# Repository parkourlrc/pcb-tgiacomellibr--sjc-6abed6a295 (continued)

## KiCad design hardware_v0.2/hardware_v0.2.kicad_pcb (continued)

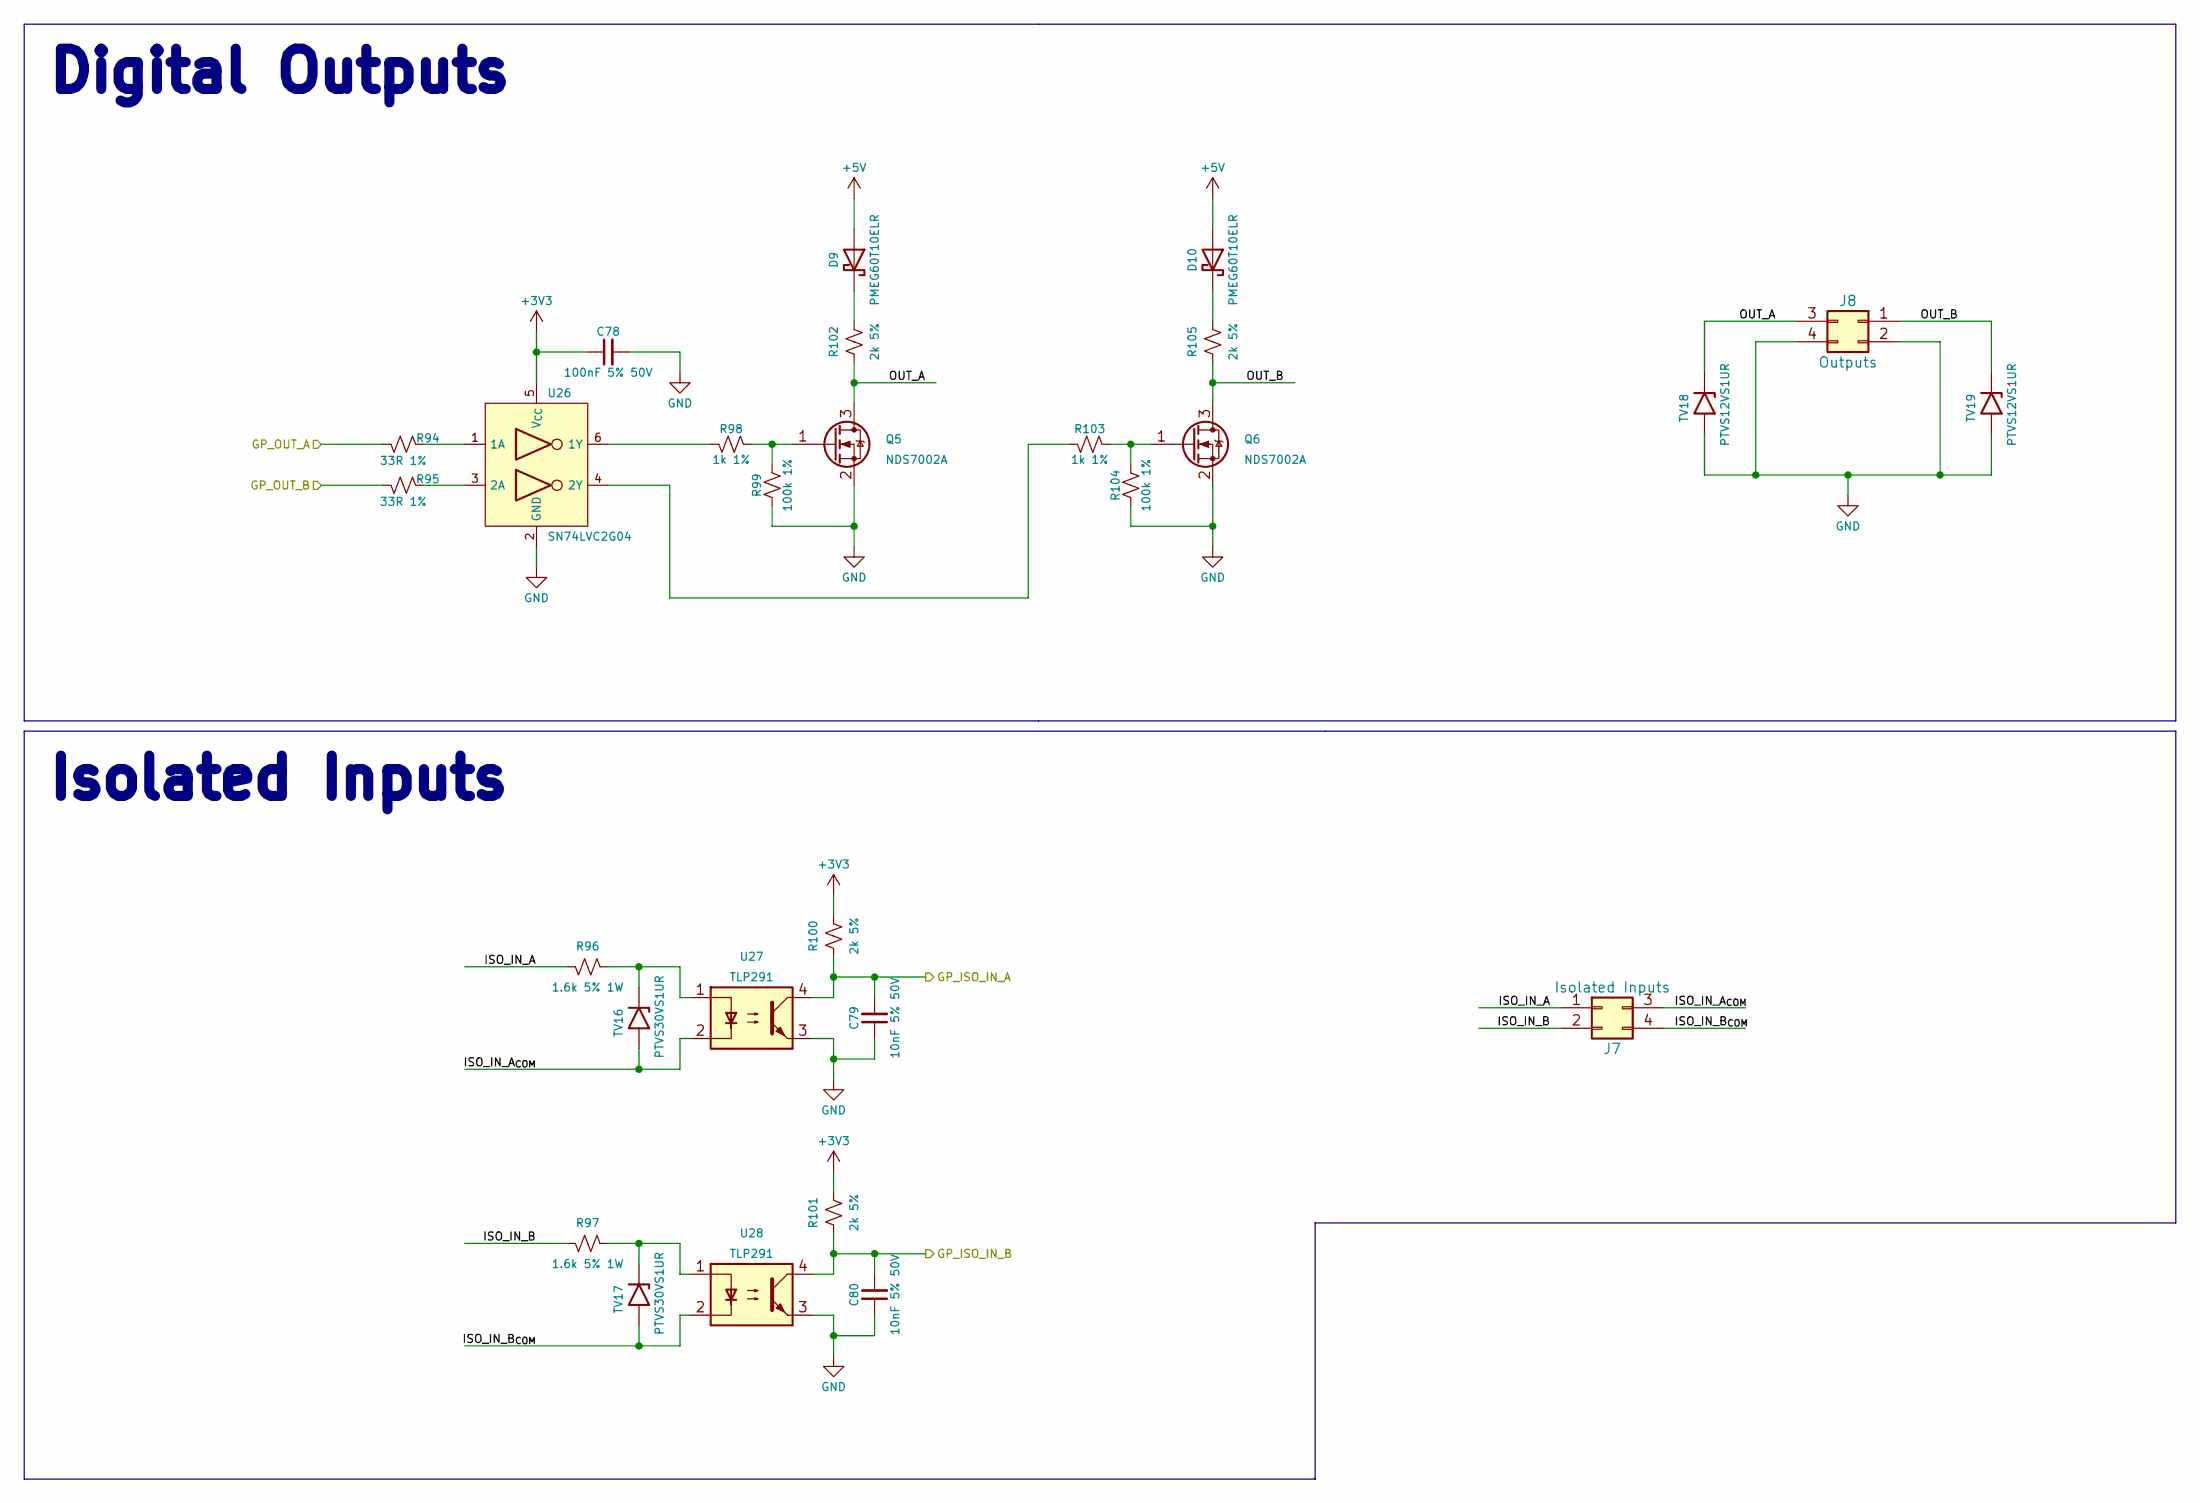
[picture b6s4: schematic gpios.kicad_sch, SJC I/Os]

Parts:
C78: 100nF 5% 50V; C_0603_1608Metric; JLCPCB Part # C91183
C79, C80: 10nF 5% 50V; C_0603_1608Metric; JLCPCB Part # C389113
D9, D10: PMEG60T10ELR; D_SOD-123F; JLCPCB Part # C552945
J7: Isolated Inputs; Molex_Micro-Fit_3.0_43045-0412_2x02_P3.00mm_Vertical
J8: Outputs; Molex_Micro-Fit_3.0_43045-0412_2x02_P3.00mm_Vertical
Q5, Q6: NDS7002A; SOT-23; JLCPCB Part # C74715
R94, R95: 33R 1%; R_0603_1608Metric; JLCPCB Part # C108661
R96, R97: 1.6k 5% 1W; R_2512_6332Metric_Pad1.40x3.35mm_HandSolder; JLCPCB Part # C453392
R98, R103: 1k 1%; R_0603_1608Metric; JLCPCB Part # C22548
R99, R104: 100k 1%; R_0603_1608Metric; JLCPCB Part # C14675
R100, R101, R102, R105: 2k 5%; R_0603_1608Metric; JLCPCB Part # C103396
TV16, TV17: PTVS30VS1UR; D_SOD-123; JLCPCB Part # C553410
TV18, TV19: PTVS12VS1UR; D_SOD-123; JLCPCB Part # C456115
U26: SN74LVC2G04; SOT-23-6_Handsoldering; JLCPCB Part # C10428
U27, U28: TLP291; SOP-4_4.4x2.6mm_P1.27mm; JLCPCB Part # C55144

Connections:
+3V3: C78.1, R100.2, R101.2, U26.5 (V_{CC}); also elsewhere on the board
+5V: D9.2 (A), D10.2 (A); also elsewhere on the board
/Control/GP_ISO_IN_A: C79.2, R100.1, U27.4; also elsewhere on the board
/Control/GP_ISO_IN_B: C80.2, R101.1, U28.4; also elsewhere on the board
/Control/GP_OUT_A: R94.2; also elsewhere on the board
/Control/GP_OUT_B: R95.2; also elsewhere on the board
/GPIOs/ISO_IN_A: J7.1, R96.2
/GPIOs/ISO_IN_A_{COM}: J7.3, TV16.2 (A), U27.2
/GPIOs/ISO_IN_B: J7.2, R97.2
/GPIOs/ISO_IN_B_{COM}: J7.4, TV17.2 (A), U28.2
/GPIOs/OUT_A: J8.3, Q5.3 (D), R102.1, TV18.1 (K)
/GPIOs/OUT_B: J8.1, Q6.3 (D), R105.1, TV19.1 (K)
GND: C78.2, C79.1, C80.1, J8.2, J8.4, Q5.2 (S), Q6.2 (S), R99.1, R104.1, TV18.2 (A), TV19.2 (A), U26.2 (GND), U27.3, U28.3; also elsewhere on the board
unnamed: D9.1 (K), R102.2
unnamed: D10.1 (K), R105.2
unnamed: Q5.1 (G), R98.1, R99.2
unnamed: Q6.1 (G), R103.1, R104.2
unnamed: R96.1, TV16.1 (K), U27.1
unnamed: R97.1, TV17.1 (K), U28.1
unnamed: R94.1, U26.1 (1A)
unnamed: R98.2, U26.6 (1Y)
unnamed: R95.1, U26.3 (2A)
unnamed: R103.2, U26.4 (2Y)

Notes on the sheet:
Isolated Inputs
Digital Outputs

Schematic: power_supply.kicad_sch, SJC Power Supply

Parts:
C14, C15, C30, C31, C34: 100nF 5% 50V; C_0603_1608Metric; JLCPCB Part # C91183
C16, C33, C35, C36: 10nF 5% 50V; C_0603_1608Metric; JLCPCB Part # C389113
C17, C18: 47uF 63V 20%; CP_Elec_8x10.5; JLCPCB Part # C116428
C19, C20, C21, C22, C26, C27, C29, C32: 10uF 10% 50V; C_1206_3216Metric; JLCPCB Part # C13585
C23, C24: 1uF 10% 50V; C_1206_3216Metric; JLCPCB Part # C1848
C25, C28: 22uF 10% 25V; C_1206_3216Metric; JLCPCB Part # C105213
C37, C38: 680uF 63V 20%; CP_Elec_18x17.5; JLCPCB Part # C249956
D1: PMEG60T20ELR; D_SOD-123F; JLCPCB Part # C552947
F1: 25A 32V; Fuse_1206_3216Metric_Pad1.42x1.75mm_HandSolder; JLCPCB Part # C2925001
FB3, FB4, FB5, FB6: 220R 3A; L_0805_2012Metric_Pad1.05x1.20mm_HandSolder; JLCPCB Part # C76818
J2: V_{POWER}; AMASS_XT60PW-M_1x02_P7.20mm_Horizontal; JLCPCB Part # C98732
LD1, LD2, LD3, LD4, LD5, LD6: 1.8V @ 5mA; LED_0603_1608Metric_Pad1.05x0.95mm_HandSolder; JLCPCB Part # C165982
Q1, Q2, Q4: SI7149ADP; PowerPAK_SO-8_Single; JLCPCB Part # C554002
Q3: NDS7002A; SOT-23; JLCPCB Part # C74715
R11, R17, R19, R23, R24: 100k 1%; R_0603_1608Metric; JLCPCB Part # C14675
R12, R20, R25: 82k 0.1%; R_0603_1608Metric; JLCPCB Part # C728598
R13: 2k 5%; R_0603_1608Metric; JLCPCB Part # C103396
R14: 2k7 1%; R_0603_1608Metric; JLCPCB Part # C114612
R15: 680R 1%; R_0603_1608Metric; JLCPCB Part # C2097840
R16, R21: 330R 1%; R_0603_1608Metric; JLCPCB Part # C144102
R18: 33R 1%; R_0603_1608Metric; JLCPCB Part # C108661
R22: 1k 1%; R_0603_1608Metric; JLCPCB Part # C22548
R26: 5.62k 5% 250mW; R_0805_2012Metric_Pad1.20x1.40mm_HandSolder; JLCPCB Part # C425493
TV2: PTVS5V0S1UR; D_SOD-123; JLCPCB Part # C478011
TV3: PTVS3V3S1UR; D_SOD-123; JLCPCB Part # C183521
TV4: SMBJ30A; D_SMB_Handsoldering; JLCPCB Part # C83851
U3: VXO78015-1000; CONV_VXO78015-1000; Mouser # 490-VXO7815-1000
U4: VXO78012-1000; CONV_VXO78012-1000; Mouser # 490-VXO7812-1000
U5: NCP1117DT50; TO-252-2; JLCPCB Part # C152470
U6: NCP1117DT33; TO-252-2; JLCPCB Part # C152529
U7: SN74LVC2G04; SOT-23-6_Handsoldering; JLCPCB Part # C10428

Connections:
+3V3: C27.2, C31.2, C34.1, LD4.2 (A), R17.2, TV3.1 (K), U6.2 (VO), U7.5 (V_{CC}); also elsewhere on the board
+5V: C26.2, C30.2, LD3.2 (A), TV2.1 (K), U5.2 (VO); also elsewhere on the board
+12V: C14.2, C15.2, C25.2, C29.2, FB3.2, FB5.1, LD1.2 (A), U4.3 (+V_{OUT})
+15V: C28.2, C32.2, LD2.2 (A), U3.3 (+V_{OUT}); also elsewhere on the board
/Control/SYS_HEARTBEAT: R18.1; also elsewhere on the board
/Control/V_{MOTOR}_~EN: C33.2, R17.1, U7.1 (1A); also elsewhere on the board
/Power Supply/12V_REG_IN: C18.1, C22.2, D1.1 (K), U4.1 (+V_{IN})
/Power Supply/15V_REG_IN: C16.2, C17.1, C21.2, Q1.1 (S), Q1.2 (S), Q1.3 (S), R11.2, U3.1 (+V_{IN})
GND: C19.1, C20.1, C23.1, C24.1, C26.1, C27.1, C30.1, C31.1, C33.1, C34.2, FB4.1, FB6.1, R15.2, R16.2, R21.2, TV2.2 (A), TV3.2 (A), U5.1 (GND), U6.1 (GND), U7.2 (GND); also elsewhere on the board
unnamed: LD1.1 (K), R13.1
unnamed: LD2.1 (K), R14.1
unnamed: LD3.1 (K), R15.1
unnamed: LD4.1 (K), R16.1
unnamed: LD5.2 (A), U7.4 (2Y)
unnamed: LD5.1 (K), R21.1
unnamed: LD6.1 (K), R26.1
unnamed: C16.1, Q1.4 (G), R11.1, R12.2
unnamed: C35.1, Q2.4 (G), R19.1, R20.2
unnamed: Q3.3 (D), R25.1
unnamed: Q3.1 (G), R22.1, R23.2
unnamed: C36.1, Q4.4 (G), R24.1, R25.2
unnamed: C19.2, C23.2, FB3.1, U5.3 (VI)
unnamed: C20.2, C24.2, FB5.2, U6.3 (VI)
unnamed: R22.2, U7.6 (1Y)
unnamed: R18.2, U7.3 (2A)
PGND: C14.1, C15.1, C17.2, C18.2, C21.1, C22.1, C25.1, C28.1, C29.1, C32.1, C37.2, C38.2, FB4.2, FB6.2, J2.2, Q3.2 (S), R12.1, R13.2, R14.2, R20.1, R23.1, R26.2, TV4.2 (A), U3.2 (GND), U4.2 (GND); also elsewhere on the board
V_{DC}+: C35.2, C36.2, D1.2 (A), Q1.5 (D), Q2.1 (S), Q2.2 (S), Q2.3 (S), Q4.1 (S), Q4.2 (S), Q4.3 (S), R19.2, R24.2
V_{MOTOR}: C37.1, C38.1, LD6.2 (A), Q4.5 (D); also elsewhere on the board
V_{PWR}+: F1.1, J2.1
V_{PWR}_Fuse+: F1.2, Q2.5 (D), TV4.1 (K)

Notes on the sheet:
Power flags
Power Inputs
Input: 24 V Range: (18-30 V)

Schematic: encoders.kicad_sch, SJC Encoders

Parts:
C66, C67: 22nF 5% 50V; C_0603_1608Metric; JLCPCB Part # C277528
C68, C69: 1uF 10% 50V; C_1206_3216Metric; JLCPCB Part # C1848
C70, C71, C72, C73, C74, C75, C76, C77: 100nF 5% 50V; C_0603_1608Metric; JLCPCB Part # C91183
J5: Joint encoders; Molex_Micro-Fit_3.0_43045-0812_2x04_P3.00mm_Vertical
J6: Aux. encoders; Molex_Micro-Fit_3.0_43045-0812_2x04_P3.00mm_Vertical
R72, R73, R74, R75, R77, R78, R82, R83, R88, R89: 2k7 1%; R_0603_1608Metric; JLCPCB Part # C114612
R76, R80: 1.5k 1%; R_0603_1608Metric; JLCPCB Part # C285210
R79, R81: 1k 1%; R_0603_1608Metric; JLCPCB Part # C22548
R84, R85, R86, R87, R90, R91, R92, R93: 33R 1%; R_0603_1608Metric; JLCPCB Part # C108661
SB10, SB11, SB12, SB13, SB14, SB15, SB16, SB17: SolderJumper-2_P1.3mm_Open_RoundedPad1.0x1.5mm
TV6, TV7, TV8, TV10, TV12, TV13, TV15: PTVS5V0S1UR; D_SOD-123; JLCPCB Part # C478011
TV9, TV11, TV14: PTVS12VS1UR; D_SOD-123; JLCPCB Part # C456115
U22, U23, U24, U25: 74LVC2T45DC; VSSOP-8_2.3x2mm_P0.5mm; JLCPCB Part # C730237

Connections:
+3V3: C72.1, C73.1, C76.2, C77.1, U22.1 (VCCA), U23.1 (VCCA), U24.1 (VCCA), U25.1 (VCCA); also elsewhere on the board
+5V: C68.2, C69.2, C70.2, C71.2, C74.1, C75.2, J5.5, J5.7, J6.5, J6.7, R72.1, R73.1, R74.1, R75.1, R77.2, R78.2, TV14.1 (K), TV15.1 (K), U22.8 (VCCB), U23.8 (VCCB), U24.8 (VCCB), U25.8 (VCCB); also elsewhere on the board
/Control/AUX1_ENC_CH1: R92.1; also elsewhere on the board
/Control/AUX1_ENC_CH2: R93.1; also elsewhere on the board
/Control/AUX2_ENC_CH1: R86.1; also elsewhere on the board
/Control/AUX2_ENC_CH2: R87.1; also elsewhere on the board
/Control/JOINT_ENC_CH1: R85.1; also elsewhere on the board
/Control/JOINT_ENC_CH2: R84.1; also elsewhere on the board
/Control/JOINT_SW_L: R90.1; also elsewhere on the board
/Control/JOINT_SW_R: R91.1; also elsewhere on the board
/Encoders/JNT_ENC_A: J5.3, SB14.1 (A), TV11.1 (K), U22.6 (2B)
/Encoders/JNT_ENC_B: J5.4, SB15.1 (A), TV9.1 (K), U22.7 (1B)
/Encoders/JNT_ESTOP_A: J5.2, R76.1
/Encoders/JNT_ESTOP_B: J5.1, R80.1
/Encoders/JNT_SW_A: C66.2, R76.2, R79.1, TV6.1 (K), U24.7 (1B)
/Encoders/JNT_SW_B: C67.2, R80.2, R81.1, TV13.1 (K), U24.6 (2B)
/Encoders/S1_ENC_A: J6.4, SB13.1 (A), TV7.1 (K), U25.7 (1B)
/Encoders/S1_ENC_B: J6.3, SB12.1 (A), TV8.1 (K), U25.6 (2B)
/Encoders/S2_ENC_A: J6.2, SB11.1 (A), TV10.1 (K), U23.7 (1B)
/Encoders/S2_ENC_B: J6.1, SB10.1 (A), TV12.1 (K), U23.6 (2B)
GND: C66.1, C67.1, C68.1, C69.1, C70.1, C71.1, C72.2, C73.2, C74.2, C75.1, C76.1, C77.2, J5.6, J5.8, J6.6, J6.8, R82.1, R83.1, R88.1, R89.1, SB16.2 (B), SB17.2 (B), TV6.2 (A), TV7.2 (A), TV8.2 (A), TV9.2 (A), TV10.2 (A), TV11.2 (A), TV12.2 (A), TV13.2 (A), TV14.2 (A), TV15.2 (A), U22.4 (GND), U23.4 (GND), U24.4 (GND), U25.4 (GND); also elsewhere on the board
unnamed: R72.2, SB10.2 (B)
unnamed: R73.2, SB11.2 (B)
unnamed: R74.2, SB12.2 (B)
unnamed: R75.2, SB13.2 (B)
unnamed: R77.1, SB14.2 (B)
unnamed: R78.1, SB15.2 (B)
unnamed: R79.2, SB16.1 (A)
unnamed: R81.2, SB17.1 (A)
unnamed: R84.2, U22.2 (1A)
unnamed: R85.2, U22.3 (2A)
unnamed: R82.2, U22.5 (DIR)
unnamed: R86.2, U23.2 (1A)
unnamed: R87.2, U23.3 (2A)
unnamed: R83.2, U23.5 (DIR)
unnamed: R90.2, U24.2 (1A)
unnamed: R91.2, U24.3 (2A)
unnamed: R88.2, U24.5 (DIR)
unnamed: R92.2, U25.2 (1A)
unnamed: R93.2, U25.3 (2A)
unnamed: R89.2, U25.5 (DIR)

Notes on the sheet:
33R 1% 100mW
Encoder interfaces

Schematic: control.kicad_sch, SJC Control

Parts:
C1: 10uF 10% 50V; C_1206_3216Metric; JLCPCB Part # C13585
C2, C4, C6, C7, C9, C12, C13: 100nF 5% 50V; C_0603_1608Metric; JLCPCB Part # C91183
C3, C5, C11: 1uF 10% 50V; C_1206_3216Metric; JLCPCB Part # C1848
C8: 10nF 5% 50V; C_0603_1608Metric; JLCPCB Part # C389113
C10: 4.7uF 10% 20V; CP_EIA-3528-15_AVX-H_Pad1.50x2.35mm_HandSolder; JLCPCB Part # C308921
FB1, FB2: 220R 3A; L_0805_2012Metric_Pad1.05x1.20mm_HandSolder; JLCPCB Part # C76818
J1: PROG_{DBG}; PinHeader_2x04_P2.54mm_Vertical; JLCPCB Part # C2884546
JP1: DEBUG_OUT_SEL; PinHeader_2x04_P2.54mm_Vertical; JLCPCB Part # C234182
JP2: E-STOP_DIV; PinHeader_1x02_P2.54mm_Vertical; JLCPCB Part # C234182
NT1, NT2: NetTie-2_SMD_Pad0.5mm
R1, R2, R3, R4, R5, R6, R7, R8: 33R 1%; R_0603_1608Metric; JLCPCB Part # C108661
R9: 100k 1%; R_0603_1608Metric; JLCPCB Part # C14675
R10: 10k 1%; R_0603_1608Metric; JLCPCB Part # C98220
SB1: CS_ADC_SEL; SolderJumper-3_P1.3mm_Bridged2Bar12_RoundedPad1.0x1.5mm
SW1: Tactile Switch; SW_Tactile_SPST_NO_Straight_CK_PTS636Sx25SMTRLFS; JLCPCB Part # C2689642
TV1: PTVS3V3S1UR; D_SOD-123; JLCPCB Part # C183521
U1: STM32F446RETx; LQFP-64_10x10mm_P0.5mm; JLCPCB Part # C69336
U2: YSO110TR-16MHz; Oscillator_SMD_YXC_YSO110TR_7050-4Pin_7.0x5.0mm; JLCPCB Part # C669093

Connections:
+3V3: C1.2, C2.2, C3.2, C4.2, C5.2, C6.2, C7.2, FB1.1, J1.2, JP2.1, NT1.1, TV1.1 (K), U1.1 (VBAT), U1.19 (VDD), U1.32 (VDD), U1.48 (VDD), U1.64 (VDD); also elsewhere on the board
+3V3A: C8.2, C9.2, C11.2, FB1.2, U1.13 (VDDA)
+3V3_OSC: C13.1, NT1.2, R10.2, U2.4 (V_{DD})
/Communication/COM_USB_D+: U1.45 (PA12); also elsewhere on the board
/Communication/COM_USB_D-: U1.44 (PA11); also elsewhere on the board
/Communication/COM_USB_V_{BUS}_SIG: U1.42 (PA9); also elsewhere on the board
/Communication/RS485_RX: U1.17 (PA3); also elsewhere on the board
/Communication/RS485_TX: U1.16 (PA2); also elsewhere on the board
/Communication/RS485_~RE_DE: U1.20 (PA4); also elsewhere on the board
/Control/AUX1_ENC_CH1: U1.22 (PA6); also elsewhere on the board
/Control/AUX1_ENC_CH2: U1.23 (PA7); also elsewhere on the board
/Control/AUX2_ENC_CH1: U1.37 (PC6); also elsewhere on the board
/Control/AUX2_ENC_CH2: U1.38 (PC7); also elsewhere on the board
/Control/BOOT: JP2.2, R9.2, U1.60 (BOOT0)
/Control/CURRENT_SIGNAL_FILT: SB1.2 (C); also elsewhere on the board
/Control/CURRENT_SIGNAL_{FILTA}: SB1.1 (A), U1.26 (PB0)
/Control/CURRENT_SIGNAL_{FILTB}: SB1.3 (B), U1.24 (PC4)
/Control/DBG_485_RX: JP1.2; also elsewhere on the board
/Control/DBG_485_TX: JP1.4; also elsewhere on the board
/Control/DBG_485_~RE: JP1.6; also elsewhere on the board
/Control/DEBUG_USART_RX: R3.1, U1.52 (PC11)
/Control/DEBUG_USART_TX: R2.1, U1.51 (PC10)
/Control/GP_ISO_IN_A: U1.8 (PC0); also elsewhere on the board
/Control/GP_ISO_IN_B: U1.9 (PC1); also elsewhere on the board
/Control/GP_OUT_A: U1.4 (PC15); also elsewhere on the board
/Control/GP_OUT_B: U1.3 (PC14); also elsewhere on the board
/Control/JOINT_ENC_CH1: U1.14 (PA0); also elsewhere on the board
/Control/JOINT_ENC_CH2: U1.15 (PA1); also elsewhere on the board
/Control/JOINT_SW_L: U1.11 (PC3); also elsewhere on the board
/Control/JOINT_SW_R: U1.10 (PC2); also elsewhere on the board
/Control/JTCK/SWCLK: R7.1, U1.49 (PA14)
/Control/JTDI: R5.1, U1.50 (PA15)
/Control/JTDO/TRACESWO: R4.1, U1.55 (PB3)
/Control/JTMS/SWDIO: R6.1, U1.46 (PA13)
/Control/L_MOT_HI_{PWM}: U1.41 (PA8); also elsewhere on the board
/Control/L_MOT_LO_{PWM}: U1.34 (PB13); also elsewhere on the board
/Control/MCU_OSC: U1.5 (PH0), U2.3 (OUT)
/Control/MOTOR_INPUT_VOLTAGE_SIG: U1.25 (PC5); also elsewhere on the board
/Control/NJTRST: R8.1, U1.56 (PB4)
/Control/NRST: C12.2, SW1.2, U1.7 (NRST)
/Control/R_MOT_HI_{PWM}: U1.43 (PA10); also elsewhere on the board
/Control/R_MOT_LO_{PWM}: U1.27 (PB1); also elsewhere on the board
/Control/SYS_HEARTBEAT: U1.53 (PC12); also elsewhere on the board
/Control/V_{MOTOR}_~EN: U1.57 (PB5); also elsewhere on the board
GND: C1.1, C2.1, C3.1, C4.1, C5.1, C6.1, C7.1, C10.2, C12.1, FB2.1, J1.1, JP1.7, JP1.8, NT2.2, R9.1, SW1.1, TV1.2 (A), U1.18 (VSS), U1.31 (VSS), U1.47 (VSS), U1.63 (VSS); also elsewhere on the board
GNDA: C8.1, C9.1, C11.1, FB2.2, U1.12 (VSSA)
GND_OSC: C13.2, NT2.1, U2.2 (GND)
unnamed: J1.3, R8.2
unnamed: J1.4, R4.2
unnamed: J1.6, R5.2
unnamed: J1.7, R7.2
unnamed: J1.8, R6.2
unnamed: JP1.1, R3.2
unnamed: JP1.3, R2.2
unnamed: JP1.5, R1.2
unnamed: R1.1, U1.54 (PD2)
unnamed: C10.1, U1.30 (VCAP_1)
unnamed: R10.1, U2.1 (En)

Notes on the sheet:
Microcontroller
33R 1%
Power flags
Debug/Prog

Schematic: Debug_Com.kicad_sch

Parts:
C94: 1uF 10% 50V; C_1206_3216Metric; JLCPCB Part # C1848
C95: 100nF 5% 50V; C_0603_1608Metric; JLCPCB Part # C91183
J11: Debug-485; PinHeader_2x02_P2.54mm_Vertical
JP4: RS-485 TERM; PinHeader_1x02_P2.54mm_Vertical; JLCPCB Part # C234182
R128, R129: 10R 1% 1/2W; R_0805_2012Metric_Pad1.20x1.40mm_HandSolder; JLCPCB Part # C441969
R130: 120R 0.1% 1/8W; R_0805_2012Metric_Pad1.20x1.40mm_HandSolder; JLCPCB Part # C2828708
TV22: SM712; SOT-23-3; JLCPCB Part # C293966
U37: SN65HVD75DR; SOIC-8_3.9x4.9mm_P1.27mm; JLCPCB Part # C57928

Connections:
+3V3: C94.1, C95.1, J11.4, U37.8 (VCC); also elsewhere on the board
/Control/DBG_485_RX: U37.1 (R); also elsewhere on the board
/Control/DBG_485_TX: U37.4 (D); also elsewhere on the board
/Control/DBG_485_~RE: U37.2 (~RE), U37.3 (DE); also elsewhere on the board
/Debug/RS485+: J11.2, R128.1, R130.1, TV22.2
/Debug/RS485-: J11.1, JP4.2, R129.1, TV22.1
/Debug/RS+: R128.2, U37.7 (B)
/Debug/RS-: R129.2, U37.6 (A)
GND: C94.2, C95.2, J11.3, TV22.3, U37.5 (GND); also elsewhere on the board
unnamed: JP4.1, R130.2

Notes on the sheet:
10R 0.5W Anti-Surge/Pulse-Proof
GND
20Mbps RS-485 Transceiver

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
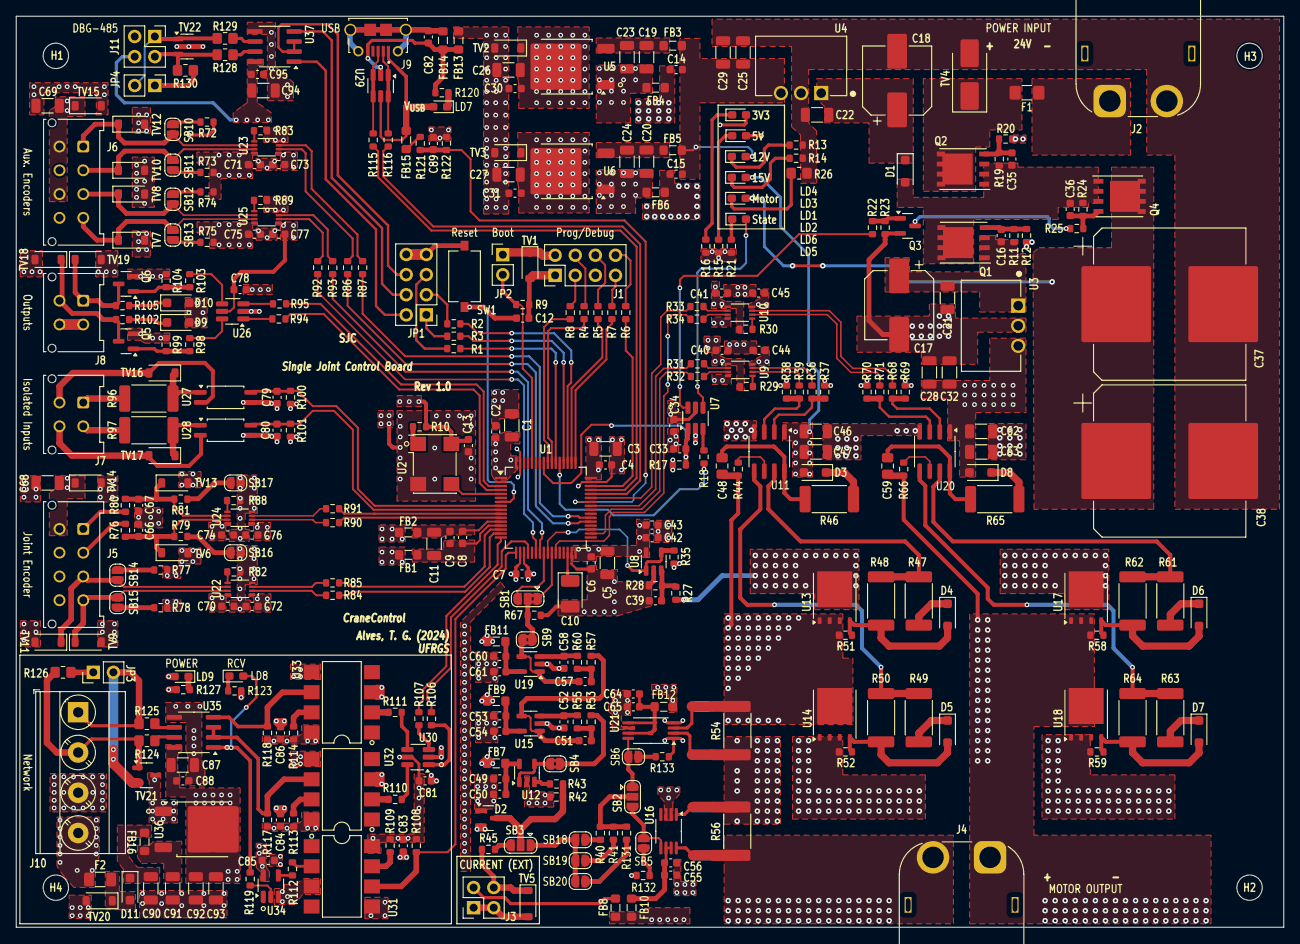
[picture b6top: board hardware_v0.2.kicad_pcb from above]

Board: 4 copper layers, 160.0 x 115.0 mm, 375 parts (0 on the bottom side), 238 nets.

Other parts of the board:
R132, R133: 10k 1%; R_0603_1608Metric

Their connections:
GND: R132.1, R133.1; also elsewhere on the board

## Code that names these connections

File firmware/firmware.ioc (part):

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Mcu.Name=STM32H723VGTx
Mcu.Package=LQFP100
Mcu.UserName=STM32H723VGTx
PA0.GPIOParameters=GPIO_Label
PA0.GPIO_Label=JOINT_ENC_CH1
PA0.Signal=S_TIM2_CH1_ETR
PA1.GPIOParameters=GPIO_Label
PA1.GPIO_Label=JOINT_ENC_CH2
PA1.Signal=S_TIM2_CH2
PA10.GPIOParameters=GPIO_Label
PA10.GPIO_Label=FDCAN_ACT
PA10.Signal=GPIO_Output
PA11.Mode=FDCAN_Activate
PA11.Signal=FDCAN1_RX
PA12.Mode=FDCAN_Activate
PA12.Signal=FDCAN1_TX
PA13(JTMS/SWDIO).Mode=JTAG_5_pins
PA13(JTMS/SWDIO).Signal=DEBUG_JTMS-SWDIO
PA14(JTCK/SWCLK).Mode=JTAG_5_pins
PA14(JTCK/SWCLK).Signal=DEBUG_JTCK-SWCLK
PA15(JTDI).Mode=JTAG_5_pins
PA15(JTDI).Signal=DEBUG_JTDI
PA6.GPIOParameters=GPIO_Label
PA6.GPIO_Label=AUX1_ENC_CH2
PA6.Signal=S_TIM3_CH1
PA7.GPIOParameters=GPIO_Label
PA7.GPIO_Label=AUX1_ENC_CH1
PA7.Signal=S_TIM3_CH2
PA8.GPIOParameters=GPIO_Label
PA8.GPIO_Label=SPI_INT
PA8.Signal=GPXTI8
PA9.GPIOParameters=GPIO_Label
PA9.GPIO_Label=SPI_SCK
PA9.Mode=Full_Duplex_Master
PA9.Signal=SPI2_SCK
PB0.GPIOParameters=GPIO_Label
PB0.GPIO_Label=L_MOT_LO
PB0.Mode=PWM Generation2 CH2 CH2N
PB0.Signal=TIM1_CH2N
PB10.GPIOParameters=GPIO_Label
PB10.GPIO_Label=COM_485_TX
PB10.Mode=Asynchronous
PB10.Signal=USART3_TX
PB11.GPIOParameters=GPIO_Label
PB11.GPIO_Label=COM_485_RX
PB11.Mode=Asynchronous
PB11.Signal=USART3_RX
PB12.GPIOParameters=GPIO_Label
PB12.GPIO_Label=AUX_USART_RX
PB12.Mode=Asynchronous
PB12.Signal=UART5_RX
PB13.GPIOParameters=GPIO_Label
PB13.GPIO_Label=AUX_USART_TX
PB13.Mode=Asynchronous
PB13.Signal=UART5_TX
PB14.GPIOParameters=GPIO_Label
PB14.GPIO_Label=COM_485_DE
PB14.Mode=Hardware Flow Control (RS485)
PB14.Signal=USART3_DE
PB15.GPIOParameters=GPIO_Label
PB15.GPIO_Label=COM_485_ACT
PB15.Signal=GPIO_Output
PB3(JTDO/TRACESWO).Mode=JTAG_5_pins
PB3(JTDO/TRACESWO).Signal=DEBUG_JTDO-SWO
PB4(NJTRST).Mode=JTAG_5_pins
PB4(NJTRST).Signal=DEBUG_JTRST
PB5.GPIOParameters=GPIO_Label
PB5.GPIO_Label=I2C1_INT
PB5.Signal=GPXTI5
PB6.Mode=I2C
PB6.Signal=I2C1_SCL
PB7.Mode=I2C
PB7.Signal=I2C1_SDA
PC0.GPIOParameters=GPIO_Label
PC0.GPIO_Label=JOINT_SW_R
PC0.Signal=GPXTI0
PC1.GPIOParameters=GPIO_Label
PC1.GPIO_Label=JOINT_SW_L
PC1.Signal=GPXTI1
PC10.GPIOParameters=GPIO_Label
PC10.GPIO_Label=DEBUG_USART_TX
PC10.Mode=Asynchronous
PC10.Signal=UART4_TX
PC11.GPIOParameters=GPIO_Label
PC11.GPIO_Label=DEBUG_USART_RX
PC11.Mode=Asynchronous
PC11.Signal=UART4_RX
PC2_C.Mode=Full_Duplex_Master
PC2_C.Signal=SPI2_MISO
PC3_C.Mode=Full_Duplex_Master
PC3_C.Signal=SPI2_MOSI
PC8.GPIOParameters=GPIO_Label
PC8.GPIO_Label=SPI_RST
PC8.Signal=GPIO_Output
PC9.GPIOParameters=GPIO_Label
PC9.GPIO_Label=SPI_CSEL
PC9.Signal=GPIO_Output
PD12.GPIOParameters=GPIO_Label
PD12.GPIO_Label=AUX2_ENC_CH1
PD12.Signal=S_TIM4_CH1
PD13.GPIOParameters=GPIO_Label
PD13.GPIO_Label=AUX2_ENC_CH2
PD13.Signal=S_TIM4_CH2
PE0.GPIOParameters=GPIO_Label
PE0.GPIO_Label=GP_OUT_A
PE0.Signal=GPIO_Output
PE1.GPIOParameters=GPIO_Label
PE1.GPIO_Label=GP_OUT_B
PE1.Signal=GPIO_Output
PE10.GPIOParameters=GPIO_Label
PE10.GPIO_Label=MotorDriver_EN
PE10.Signal=GPIO_Output
PE11.GPIOParameters=GPIO_Label
PE11.GPIO_Label=L_MOT_HI
PE11.Signal=S_TIM1_CH2
PE12.GPIOParameters=GPIO_Label
PE12.GPIO_Label=MotorDriverPSU_EN
PE12.Signal=GPIO_Output
PE13.GPIOParameters=GPIO_Label
PE13.GPIO_Label=MotorPSU_EN
PE13.Signal=GPIO_Output
PE8.GPIOParameters=GPIO_Label
PE8.GPIO_Label=R_MOT_LO
PE8.Mode=PWM Generation1 CH1 CH1N
PE8.Signal=TIM1_CH1N
PE9.GPIOParameters=GPIO_Label
PE9.GPIO_Label=R_MOT_HI
PE9.Signal=S_TIM1_CH1
PH0-OSC_IN.Mode=HSE-External-Clock-Source
PH0-OSC_IN.Signal=RCC_OSC_IN
RCC.HSE_VALUE=16000000
RCC.SYSCLKFreq_VALUE=550000000
RCC.SYSCLKSource=RCC_SYSCLKSOURCE_PLLCLK
board=custom

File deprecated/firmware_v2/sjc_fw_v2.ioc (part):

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Mcu.Name=STM32F446R(C-E)Tx
Mcu.Package=LQFP64
Mcu.UserName=STM32F446RETx
PA0-WKUP.GPIOParameters=GPIO_ModeDefaultPP,GPIO_Speed,GPIO_PuPd,GPIO_Label
PA0-WKUP.GPIO_Label=JOINT_ENC_CH1
PA0-WKUP.GPIO_ModeDefaultPP=GPIO_MODE_AF_PP
PA0-WKUP.GPIO_PuPd=GPIO_NOPULL
PA0-WKUP.GPIO_Speed=GPIO_SPEED_FREQ_LOW
PA0-WKUP.Signal=S_TIM2_CH1_ETR
PA1.GPIOParameters=GPIO_ModeDefaultPP,GPIO_Speed,GPIO_PuPd,GPIO_Label
PA1.GPIO_Label=JOINT_ENC_CH2
PA1.GPIO_ModeDefaultPP=GPIO_MODE_AF_PP
PA1.GPIO_PuPd=GPIO_NOPULL
PA1.GPIO_Speed=GPIO_SPEED_FREQ_LOW
PA1.Signal=S_TIM2_CH2
PA10.GPIOParameters=GPIO_ModeDefaultPP,GPIO_Speed,GPIO_PuPd,GPIO_Label
PA10.GPIO_Label=R_MOT_HI
PA10.GPIO_ModeDefaultPP=GPIO_MODE_AF_PP
PA10.GPIO_PuPd=GPIO_NOPULL
PA10.GPIO_Speed=GPIO_SPEED_FREQ_VERY_HIGH
PA10.Signal=S_TIM1_CH3
PA11.GPIOParameters=GPIO_Label
PA11.GPIO_Label=COM_USB_DM
PA11.Mode=Device_Only
PA11.Signal=USB_OTG_FS_DM
PA12.GPIOParameters=GPIO_Label
PA12.GPIO_Label=COM_USB_DP
PA12.Mode=Device_Only
PA12.Signal=USB_OTG_FS_DP
PA13.Mode=Serial_Wire
PA13.Signal=SYS_JTMS-SWDIO
PA14.Mode=Serial_Wire
PA14.Signal=SYS_JTCK-SWCLK
PA2.GPIOParameters=GPIO_Label
PA2.GPIO_Label=RS485_TX
PA2.Mode=Asynchronous
PA2.Signal=USART2_TX
PA3.GPIOParameters=GPIO_Label
PA3.GPIO_Label=RS485_RX
PA3.Mode=Asynchronous
PA3.Signal=USART2_RX
PA4.GPIOParameters=GPIO_Speed,PinState,GPIO_Label
PA4.GPIO_Label=RS485_DE
PA4.GPIO_Speed=GPIO_SPEED_FREQ_VERY_HIGH
PA4.PinState=GPIO_PIN_SET
PA4.Signal=GPIO_Output
PA6.GPIOParameters=GPIO_Label
PA6.GPIO_Label=AUX1_ENC_CH1
PA6.Signal=S_TIM3_CH1
PA7.GPIOParameters=GPIO_Label
PA7.GPIO_Label=AUX1_ENC_CH2
PA7.Signal=S_TIM3_CH2
PA8.GPIOParameters=GPIO_ModeDefaultPP,GPIO_Speed,GPIO_PuPd,GPIO_Label
PA8.GPIO_Label=L_MOT_HI
PA8.GPIO_ModeDefaultPP=GPIO_MODE_AF_PP
PA8.GPIO_PuPd=GPIO_NOPULL
PA8.GPIO_Speed=GPIO_SPEED_FREQ_VERY_HIGH
PA8.Signal=S_TIM1_CH1
PA9.GPIOParameters=GPIO_Label
PA9.GPIO_Label=COM_USB_VBUS_SIG
PA9.Signal=USB_OTG_FS_VBUS
PB0.Signal=ADCx_IN8
PB1.GPIOParameters=GPIO_ModeDefaultPP,GPIO_Speed,GPIO_PuPd,GPIO_Label
PB1.GPIO_Label=R_MOT_LO
PB1.GPIO_ModeDefaultPP=GPIO_MODE_AF_PP
PB1.GPIO_PuPd=GPIO_NOPULL
PB1.GPIO_Speed=GPIO_SPEED_FREQ_VERY_HIGH
PB1.Mode=PWM Generation3 CH3 CH3N
PB1.Signal=TIM1_CH3N
PB10.GPIOParameters=GPIO_Label
PB10.GPIO_Label=NET_ADDR_B
PB10.Signal=GPIO_Input
PB13.GPIOParameters=GPIO_ModeDefaultPP,GPIO_Speed,GPIO_PuPd,GPIO_Label
PB13.GPIO_Label=L_MOT_LO
PB13.GPIO_ModeDefaultPP=GPIO_MODE_AF_PP
PB13.GPIO_PuPd=GPIO_NOPULL
PB13.GPIO_Speed=GPIO_SPEED_FREQ_VERY_HIGH
PB13.Mode=PWM Generation1 CH1 CH1N
PB13.Signal=TIM1_CH1N
PB15.GPIOParameters=GPIO_Speed,GPIO_Label
PB15.GPIO_Label=SYS_HEARTBEAT
PB15.GPIO_Speed=GPIO_SPEED_FREQ_VERY_HIGH
PB15.Signal=GPIO_Output
PB2.GPIOParameters=GPIO_Label
PB2.GPIO_Label=NET_ADDR_C
PB2.Signal=GPIO_Input
PB5.GPIOParameters=GPIO_Speed,GPIO_Label
PB5.GPIO_Label=DEBUG_485_DE
PB5.GPIO_Speed=GPIO_SPEED_FREQ_VERY_HIGH
PB5.Signal=GPIO_Output
PC0.GPIOParameters=GPIO_Label
PC0.GPIO_Label=GP_ISO_IN_A
PC0.Signal=GPIO_Input
PC1.GPIOParameters=GPIO_Label
PC1.GPIO_Label=GP_ISO_IN_B
PC1.Signal=GPIO_Input
PC10.GPIOParameters=GPIO_Label
PC10.GPIO_Label=DEBUG_USART_TX
PC10.Mode=Asynchronous
PC10.Signal=USART3_TX
PC11.GPIOParameters=GPIO_Label
PC11.GPIO_Label=DEBUG_USART_RX
PC11.Mode=Asynchronous
PC11.Signal=USART3_RX
PC12.GPIOParameters=GPIO_Label
PC12.GPIO_Label=DEBUG_485_TX
PC12.Mode=Asynchronous
PC12.Signal=UART5_TX
PC13.GPIOParameters=GPIO_Label
PC13.GPIO_Label=V_MOTOR_DRIVER_nEN
PC13.Signal=GPIO_Output
PC14-OSC32_IN.GPIOParameters=GPIO_Label
PC14-OSC32_IN.GPIO_Label=GP_OUT_B
PC14-OSC32_IN.Signal=GPIO_Output
PC15-OSC32_OUT.GPIOParameters=GPIO_Label
PC15-OSC32_OUT.GPIO_Label=GP_OUT_A
PC15-OSC32_OUT.Signal=GPIO_Output
PC2.GPIOParameters=GPIO_Label
PC2.GPIO_Label=JOINT_SW_R
PC2.Signal=GPIO_Input
PC3.GPIOParameters=GPIO_Label
PC3.GPIO_Label=JOINT_SW_L
PC3.Signal=GPIO_Input
PC4.GPIOParameters=GPIO_Label
PC4.GPIO_Label=CURRENT_SIGNAL_FILT2
PC4.Signal=ADCx_IN14
PC5.GPIOParameters=GPIO_Label
PC5.GPIO_Label=MOTOR_INPUT_VOLTAGE_SIG
PC5.Signal=ADCx_IN15
PC6.GPIOParameters=GPIO_Label
PC6.GPIO_Label=AUX2_ENC_CH1
PC6.Signal=S_TIM8_CH1
PC7.GPIOParameters=GPIO_Label
PC7.GPIO_Label=AUX2_ENC_CH2
PC7.Signal=S_TIM8_CH2
PC8.GPIOParameters=GPIO_Label
PC8.GPIO_Label=NET_ADDR_A
PC8.Signal=GPIO_Input
PC9.GPIOParameters=GPIO_Speed,PinState,GPIO_PuPd,GPIO_Label,GPIO_ModeDefaultOutputPP
PC9.GPIO_Label=V_MOTOR_nEN
PC9.GPIO_ModeDefaultOutputPP=GPIO_MODE_OUTPUT_OD
PC9.GPIO_PuPd=GPIO_NOPULL
PC9.GPIO_Speed=GPIO_SPEED_FREQ_VERY_HIGH
PC9.PinState=GPIO_PIN_SET
PC9.Signal=GPIO_Output
PD2.GPIOParameters=GPIO_Label
PD2.GPIO_Label=DEBUG_485_RX
PD2.Mode=Asynchronous
PD2.Signal=UART5_RX
PH0-OSC_IN.Mode=HSE-External-Clock-Source
PH0-OSC_IN.Signal=RCC_OSC_IN
PH1-OSC_OUT.Mode=HSE-External-Clock-Source
PH1-OSC_OUT.Signal=RCC_OSC_OUT
RCC.HSE_VALUE=16000000
RCC.SYSCLKFreq_VALUE=180000000
RCC.SYSCLKSource=RCC_SYSCLKSOURCE_PLLCLK
board=custom

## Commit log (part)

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2023-06-05 Processor changed
2023-06-05 First release of production files
2023-06-06 Component updates
2023-06-06 STM32Cube project and pin assignment
2023-09-18 Stm32 peripheral updated
2023-09-18 SJC library created, PWM and Motor Voltage modules writed
2023-10-13 CubeMx Project Updated
2023-10-24 Update .gitignore file
2023-10-24 STM32CubeIDE project updates
2023-10-24 Firmware updates
2023-12-08 Octave files moved
2023-12-09 PCB updates
2023-12-09 Update LICENSE
2023-12-09 Cube project updates
2023-12-24 software library structure added
2023-12-24 Tests folder removed
2023-12-25 Communication library updated
    Added network config, runtime info and system version information
2023-12-25 Task system controller configurated
2023-12-27 Add communication features
2023-12-27 Update file format
2023-12-27 Code cleanup
2023-12-27 Update header comments
2023-12-28 Add encoder measurements
2023-12-28 Add encoder reading and bugfixes to IOs
2024-01-05 Add .zip to .gitignore file
2024-01-05 Add read-write test and bugfixes
2024-01-05 Add adc sensor measurements and USB debug printf
2024-01-05 Add driver updates
2024-01-06 Add system calcs
2024-01-06 Add code updates
2024-01-06 Add gitignore conditions
2024-01-06 Add new tests
2024-01-06 Add bugfix to analog sensors measurement timestep
2024-01-06 Test updated
2024-01-10 Add pid controller module and speed control tests
2024-01-10 Add tests with speed reference
2024-01-12 update debug config and remove tasks header files
2024-01-12 Add isr service tests
2024-01-18 Add Timer calcs
2024-01-18 Add Measurements Task and add improvements to analog measurements
2024-01-21 Add guard semaphores and code cleanup
2024-01-21 add updates to calcs
2024-01-21 Software library updates
2024-02-06 Debug output and datalogger interface changed
2024-02-06 Current sensor calcs updated
2024-02-06 Data evaluation updated
2024-02-07 Hardware revision initial commit
2024-02-08 Calcs updated
2024-02-10 Placement updates and power planes removed
2024-02-10 Peripheral configuration bugfixes
2024-02-14 Component placement updates
2024-02-24 Measurement task - Startup bugfixes
2024-02-24 Library updates
2024-02-24 Sjc library type modified (Shared)
2024-03-05 Fw and Sw code isolation
2024-03-05 CMakeLists update
2024-03-13 Mobus timer calcs updated
2024-03-13 Test applications updated
2024-03-13 Modbus timer configs updated
2024-03-13 Modbus usart configs updated
2024-03-13 Board configs updated
2024-03-13 Network configs cleanup
2024-03-13 Base configs updated
2024-03-13 Network application startup simplified
2024-03-13 Timeout library bufgix
2024-03-13 Adc measurement checkpoint updated
2024-03-13 Modbus serial port interrupts simplified
2024-03-13 Modbus timer code cleanup
2024-03-13 Network data structures updated
2024-03-13 Measurement task cleanup
2024-03-13 Network task application startup simplified
2024-03-13 Hardware and firmware project updated
2024-03-13 Debug output updates
2024-03-13 Task measurements code cleanup
2024-03-14 Add test signal data structures
2024-03-14 Add test signals module
2024-03-14 Add timebase functions
2024-03-14 Add test signals functions - Work in progress
2024-03-15 Add fast and slow pulse test signals
2024-03-15 Module cleanup
2024-03-15 Add module bugfixes
2024-03-15 Add test signals enums
2024-03-15 Add outputs to data logger
2024-03-18 Interface class updated
2024-03-18 Add input signals to control enum
2024-03-18 Add signal types to controle ref test
2024-03-18 Hardware design updates
2024-03-18 WIP updates
2024-03-18 File structure refresh
2024-03-18 Add script to download libmodbus
2024-03-23 Correct code identation
2024-03-23 Add data_logger module
    - Log transmission
    - TX DMA
2024-03-23 Change code to bare example
2024-03-23 Simplify TX interrupts
2024-03-23 Renumber components
2024-03-23 Add last routings
2024-03-23 Update response timeout config
2024-03-23 Add delay config
2024-03-23 Add current bias method
2024-03-23 Add time factor to test signals
2024-03-23 Add bugfix to output buffer
2024-03-23 Add bugfix to network porting layer
2024-03-23 Update datalogger output
2024-03-27 Add design updates
2024-03-28 Update NetTies of current sense circuit
2024-03-28 Add V_USB LED
2024-03-30 PCB design updated
2024-03-30 Add limits and bugfixes
2024-03-30 Update sampletime check measurement
2024-03-30 Modify DMA data buffer banks
2024-03-30 Add PidControllerLimits empty object
2024-03-30 Add current control to taskcontroller
2024-03-30 Improvement tests
2024-04-02 Add solder jumpers to current sense circuits outputs
2024-04-02 Add traces to current sense circuits and oscilator
2024-04-16 Make PortSerial module cleanup
2024-04-16 Update modbus communication response time
2024-04-16 Revert "Update .gitignore"
    This reverts commit e6ca9db04f698b192cf1e0c3b368a455a02e4e75.
2024-04-16 hardware development cleanup
2024-04-17 Add wait time between commands
2024-04-17 Test configs - Work in progress
2024-04-18 Add 5 us wait time between requests
2024-04-20 Firmware changes
    - Add Task high wattermark measurement
    - Add task loop time measurement
    - Change file permissions
    - Add controller initial state to detect current bias
    - Add different heartbeat codes to bias detection and runtime
2024-04-20 Add simplified register read test
2024-04-20 Add statistics
2024-04-23 Data structures updated
2024-04-24 Updated control mode structures
2024-04-26 Modify current comp. filter parameters
2024-04-26 Revert pid controller structure
2024-04-26 Add mean filter between adc data
2024-05-06 Ppdate project dirs
2024-05-15 Add sxhematic and layout updates
2024-05-15 Create firmware_v2 project
2024-05-17 Add layout and reference updates
2024-05-24 Add Hardware V2 pcb layout
2024-06-15 Add updates to project calcs
2024-06-15 Add updates do project firmware
2024-06-15 Work in progress: V2 Firmware updates
2024-07-01 Work in progress: Firmware adaptation to V2
2024-08-12 WIP: Create V3 Firmware project and update motor and psu schematic
2024-08-18 WIP: Current sense amplifiers changed
2024-08-18 WIP: Add Power supply protections
2024-08-18 WIP: Add new symbols and footprints
2024-08-18 WIP: Make schematic reorganization
2024-08-19 wip: Cleanup calcs folder
2024-08-19 wip: recover old pcb dimensions
2024-08-19 Update project
2024-10-29 Wip: Add isolated RS-485 transceiver
2024-10-31 Wip: Add LEDs
2024-12-27 WIP: Changing servo driver circuit
2024-12-29 remove libmodbus submodule
2024-12-29 Use libmodbus as system library
2025-01-05 WIP: Firmware v1 includes cleanup
2025-01-06 Add communication circuits
2025-01-07 Remove old schematic sheets
2025-01-07 Clear old PCB layout
2025-01-07 Add symbols and models
2025-01-07 Add can bus transceiver
2025-01-07 Add tvs protection to can fd interface
2025-01-09 Rename test applications
2025-01-09 Add install directives in cmake file
2025-01-10 Wip: Add LEDs for communication status and change network side transceiver's psu to 5V
2025-01-10 Add 3D model config
2025-01-10 Add hierarchical labels
2025-01-10 Update schematic and pcb
2025-01-13 WIP: Placement
2025-01-15 Wip: Design of 12V buck converter
2025-01-16 Wip: update naming conventions
2025-01-16 Wip: update software library naming conventions
2025-01-20 Move deprecated project files
2025-01-20 Add schematic and pcb design files
2025-01-20 Add initial fw project files
2025-01-23 Place network components
2025-01-23 Add LDO regulators (+5V and +3V3)
2025-01-25 WIP: Power components placement
2025-01-27 WIP: Component placement updates
2025-01-27 WIP: Placement updates
2025-02-02 WIP: New placement
2025-02-03 WIP: Psu updates
2025-02-05 Add bypass capacitors
2025-02-06 WIP: Buck psu updates
2025-02-07 WIP: Compontents placement update
2025-02-10 WIP: Components positioning update
2025-02-25 Wip: Save as KiCad 9
2025-02-26 Wip: Update Layout
2025-02-26 WIP: Updates
2025-03-05 Wip: layout reorganization
2025-03-06 Update bootstrap calcs
2025-03-06 Wip: Schematic changes - servomotor interface
2025-03-07 Wip: Selecting h-bridge mosfets and bootstrap network components. Incomplete!
2025-03-10 Wip: Refresh files
2025-03-10 WIP: Remove secondary current sensor
2025-03-11 Update external current sense circuit
2025-03-11 Remove shunt resistor and update external current sense circuit connector
2025-03-11 WIP: Structure changes
2025-03-11 Wip: Split pcbs
2025-03-17 Split project: Logic and Power
2025-03-17 Wip: SJC_Power routing
2025-03-18 Add calcs and Change RG_on and RG_off resistors
2025-03-18 WIP: Power signals update
2025-03-26 Code refactor in firmware V1
2025-03-26 Deprecated firmware V1 updates
2025-03-26 Add IAUC100N04S6N028 mosfet symbol and footprint
2025-03-26 Remove submodule 3rd_party/freemodbus
2025-03-28 Update Measurement task and create filter module
2025-03-28 Encoder module updates
2025-03-29 Add new filter structures and update the software library to allow dynamic filter adjustment
2025-03-31 Update bootstrap circuit calcs
2025-03-31 Wip: PCB Updates
2025-04-01 Add buck converter calcs script
2025-04-01 Add 3D models
2025-04-04 Update deprecated firmware v2
2025-04-05 Update software library and deprecated firmware filter config
2025-04-10 Schematic updates
2025-04-11 Deprecated firmware updates
2025-04-12 Create discrete controller module
2025-04-15 Hardware updates
2025-04-15 Dreprecated firmware v2 lib updates
2025-04-17 Add Spi interface
2025-04-21 Repo cleanup
2025-04-21 Branch cleanup
2025-04-21 Update branch structure
2025-04-21 Create calcs folder
2025-04-24 Add Lqi controller
2025-04-24 Add adc oversample and debug output in Json format
2025-04-26 ADD LQI Controller + Current observer module
2025-04-30 Bug fixes
2025-06-24 Changes @ ufrgs
2025-08-04 Add new encoder config
2025-08-05 Add defines to optimize build
2025-08-13 Add new modbus register map and library updates
2025-08-13 Remove Drivers from tracking
2025-08-13 Remove USB Drivers from tracking
2025-08-13 Update stm32cube project settings
2025-08-13 Update stm32 tasks
2025-08-13 Update helpers for modbus and system calcs
2025-08-13 Update types header
2025-08-13 Update helpers module for modbus and system calcs
2025-08-13 Update data structures
2025-08-13 Update stm32 aux files
2025-08-13 Update stm32 system interrupts module
2025-08-13 Update stm32 base firmware files
2025-08-13 update encoder joint definitions
2025-08-13 Update network configs and registers
2025-11-01 Cleanup deprecated main branch
2025-11-01 Add last firmware updates and the initial directions for V2 hardware
2025-11-01 Add alternative v1 pcb design
2025-11-16 Add realtime tools
2025-12-20 Change PPR to CPR encoder resolution specs (quadrature value)
2026-04-23 feat: DMA-based current measurement and module API cleanup
2026-04-23 chore: ignore editor/backup files and document default install prefix
2026-04-23 chore: untrack .vscode editor directories
